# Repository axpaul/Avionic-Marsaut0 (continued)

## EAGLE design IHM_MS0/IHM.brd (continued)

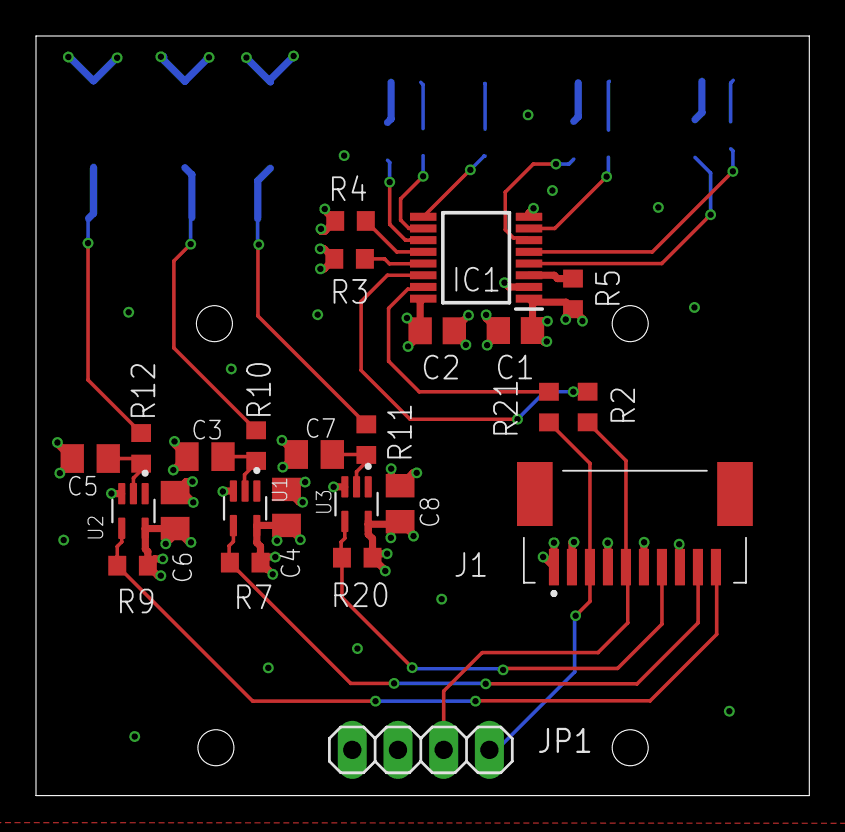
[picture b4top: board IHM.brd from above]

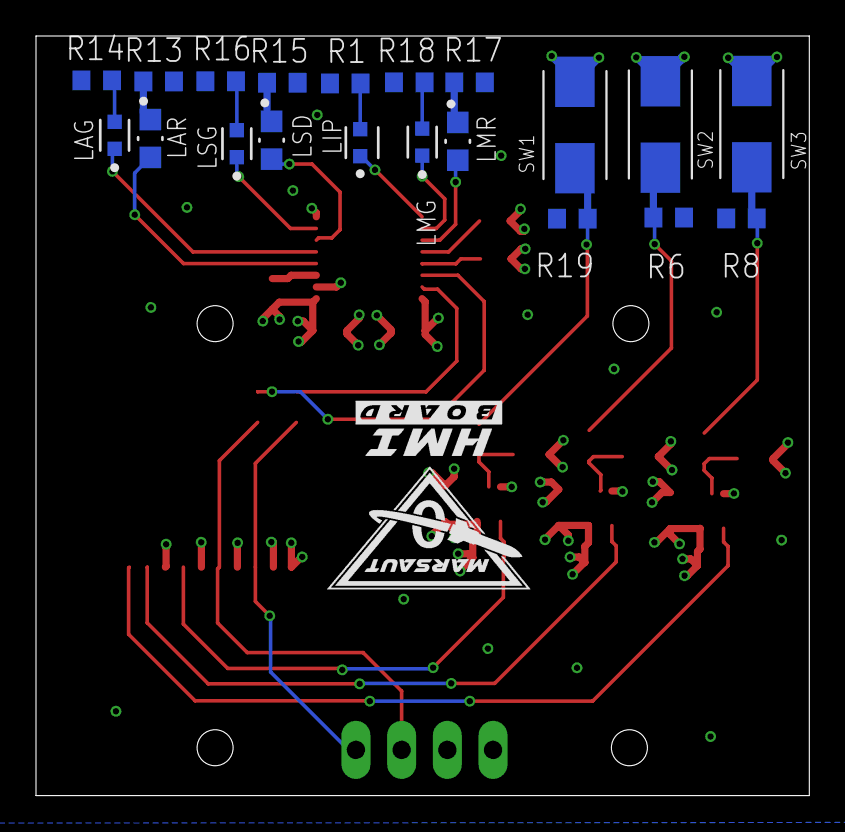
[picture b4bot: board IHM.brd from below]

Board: 4 copper layers, 43.0 x 42.2 mm, 45 parts (20 on the bottom side), 32 nets.

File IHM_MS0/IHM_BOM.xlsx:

Qty | Value | MPN | Package | Parts | Description | LCSC Part
1 |  | NON-CONNECTED | 1X04 | JP1 | PIN HEADER
3 | 0R | 0603WAF0000T5E | R0603 | R2, R4, R21 | RESISTOR, European symbol | C21189
5 | 100nF | CC0805KRX7R9BB104 | C0805K | C1, C2, C4, C6, C8 | CAPACITOR, European symbol | C49678
4 | 10K | 0603WAF1002T5E | R0603 | R3, R6, R7, R20 | RESISTOR, European symbol | C25804
7 | 110R | NON-CONNECTED | R0603 | R1, R13, R14, R15, R16, R17, R18 | RESISTOR, European symbol
3 | 147873-1 | NON-CONNECTED | SW_147873-1 | SW1, SW2, SW3 | Switch Tactile OFF (ON) SPST Rectangular Button J-Bend 0.05A 24VDC 1.77N SMD T/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
3 | 1K | 0603WAF1001T5E | R0603 | R10, R11, R12 | RESISTOR, European symbol | C21190
3 | 2u2F | 0805F225M500NT | C0805K | C3, C5, C7 | CAPACITOR, European symbol | C49217
1 | 4K7 | 0603WAF4701T5E | R0603 | R5 | RESISTOR, European symbol | C23162
3 | BROADCOM_ASMT-RF45-AN002BROADCOM_ASMT-RF45-AN002_0_0 | NON-CONNECTED | BROADCOM_ASMT-RF45-AN002_0 | LAG, LMG, LSG | LED YLW/GREEN DIFFUSED 0603 SMD
1 | BROADCOM_HSMA-C190BROADCOM_HSMA-C190_0_0 | NON-CONNECTED | BROADCOM_HSMA-C190_0 | LIP | Amber 592nm LED Indication - Discrete 1.9V 0603 (1608 Metric)
3 | BROADCOM_HSMH-C170BROADCOM_HSMH-C170_0_0 | NON-CONNECTED | BROADCOM_HSMH-C170_0 | LAR, LMR, LSD | LED RED DIFFUSED 0805 SMD
1 | FC1-10-02-T-WT-TR | NON-CONNECTED | FC11002TWTTR | J1 | FFC & FPC Connectors 1.00 mm Flat Flexible Cable (FFC) Socket Strip
3 | SN74LVC1G17DCKR | NON-CONNECTED | SOT65P210X110-5N | U1, U2, U3 | Check prices
1 | TCA6408AQPWRQ1 | NON-CONNECTED | SOP65P640X120-16N | IC1 | Automotive Low-Voltage 8-Bit I2C and SMBus I/O Expander With Interrupt Output

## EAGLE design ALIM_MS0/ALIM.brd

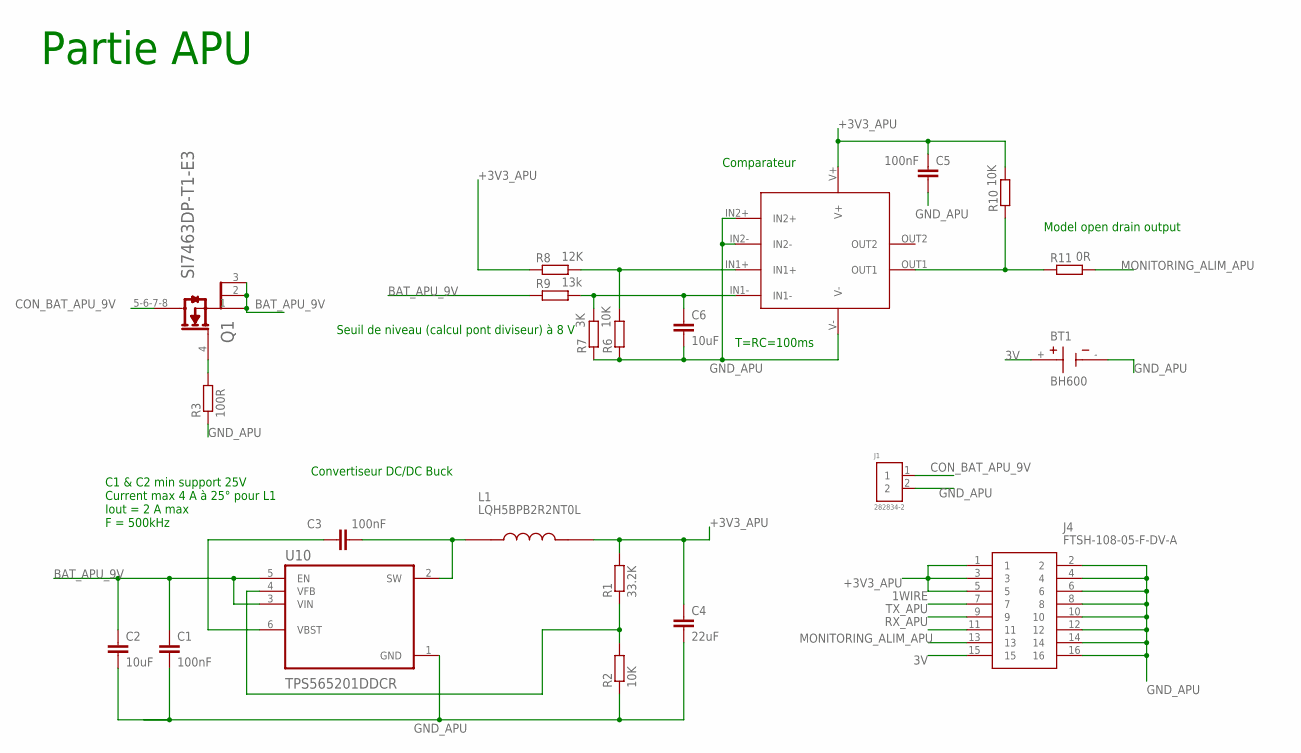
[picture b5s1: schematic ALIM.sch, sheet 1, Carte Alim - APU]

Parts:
BT1: BH600; BAT_BH600
C1, C3, C5: 100nF; C0805
C2, C6: 10uF; C0805
C4: 22uF; C0805
J1: 282834-2; CONN_282834-2
J4: FTSH-108-05-F-DV-A; FTSH-108-XX-YYY-DV-A
L1: LQH5BPB2R2NT0L; IND_LQH5BPB2R2NT0L
Q1: VISHAY_SI7463DP-T1-E3VISHAY_SI7463DP-T1-E3_0_0; VISHAY_SI7463DP-T1-E3_0
R1: 33.2K; R0603
R2, R6, R10: 10K; R0603
R3: 100R; R0603
R7: 3K; R0603
R8: 12K; R0603
R9: 13k; R0603
R11: 0R; R0603
TLV1: TLV9022
U10: TPS565201DDCR; SOT95P280X110-6N

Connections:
1WIRE: J4.7
3V: BT1.+, J4.15
+3V3_APU: C4.1, C5.1, J4.1, J4.3, J4.5, L1.2, R1.2, R8.1, R10.2, TLV1.V+
BAT_APU_9V: C1.1, C2.1, Q1.1 (1_S), Q1.2 (2_S), Q1.3 (3_S), R9.1, U10.3 (VIN), U10.5 (EN)
CON_BAT_APU_9V: J1.1, Q1.5-6-7-8 (D)
GND_APU: BT1.-, C1.2, C2.2, C4.2, C5.2, C6.2, J1.2, J4.2, J4.4, J4.6, J4.8, J4.10, J4.12, J4.14, J4.16, R2.1, R3.1, R6.1, R7.1, TLV1.IN2+, TLV1.IN2-, TLV1.V-, U10.1 (GND)
MONITORING_ALIM_APU: J4.13, R11.2
unnamed: Q1.4 (G), R3.2
unnamed: C3.1, U10.6 (VBST)
unnamed: C3.2, L1.1, U10.2 (SW)
unnamed: R1.1, R2.2, U10.4 (VFB)
unnamed: R6.2, R8.2, TLV1.IN1+
unnamed: C6.1, R7.2, R9.2, TLV1.IN1-
unnamed: R10.1, R11.1, TLV1.OUT1
RX_APU: J4.11
TX_APU: J4.9

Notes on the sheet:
C1 & C2 min support 25V Current max 4 A à 25° pour L1 Iout = 2 A max F = 500kHz
Model open drain output
T=RC=100ms
Comparateur
Convertiseur DC/DC Buck
Seuil de niveau (calcul pont diviseur) à 8 V
Partie APU

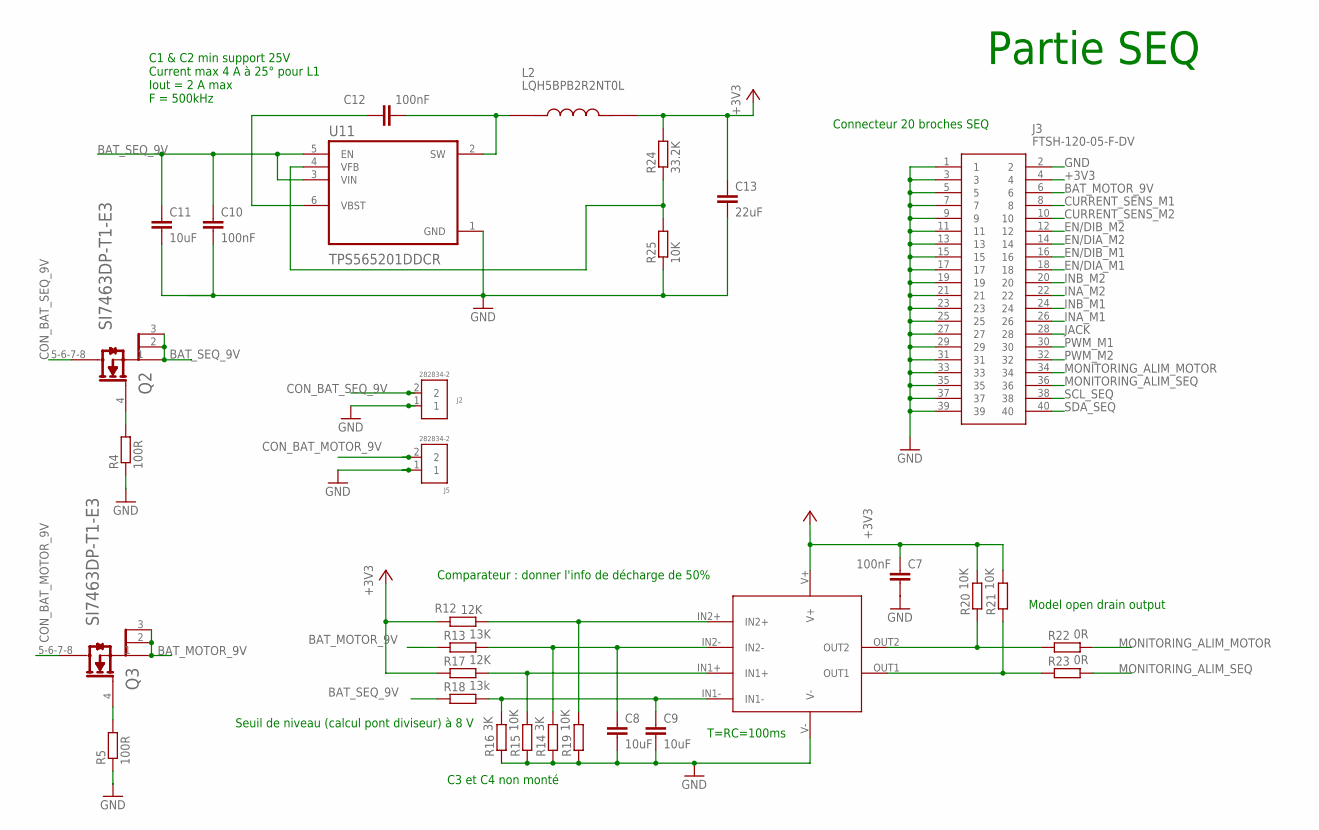
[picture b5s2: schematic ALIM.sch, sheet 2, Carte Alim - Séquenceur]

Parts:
C7, C10, C12: 100nF; C0805
C8, C9, C11: 10uF; C0805
C13: 22uF; C0805
J2, J5: 282834-2; CONN_282834-2
J3: FTSH-120-05-F-DV; FTSH-120-XX-YYY-DV
L2: LQH5BPB2R2NT0L; IND_LQH5BPB2R2NT0L
Q2, Q3: VISHAY_SI7463DP-T1-E3VISHAY_SI7463DP-T1-E3_0_0; VISHAY_SI7463DP-T1-E3_0
R4, R5: 100R; R0603
R12, R17: 12K; R0603
R13: 13K; R0603
R14, R16: 3K; R0603
R15, R19, R20, R21, R25: 10K; R0603
R18: 13k; R0603
R22, R23: 0R; R0603
R24: 33.2K; R0603
TLV2: TLV9022
U11: TPS565201DDCR; SOT95P280X110-6N

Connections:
+3V3: C7.1, C13.1, J3.4, L2.2, R12.2, R17.1, R20.2, R21.2, R24.2, TLV2.V+
BAT_MOTOR_9V: J3.6, Q3.1 (1_S), Q3.2 (2_S), Q3.3 (3_S), R13.1
BAT_SEQ_9V: C10.1, C11.1, Q2.1 (1_S), Q2.2 (2_S), Q2.3 (3_S), R18.1, U11.3 (VIN), U11.5 (EN)
CON_BAT_MOTOR_9V: J5.2, Q3.5-6-7-8 (D)
CON_BAT_SEQ_9V: J2.2, Q2.5-6-7-8 (D)
CURRENT_SENS_M1: J3.8
CURRENT_SENS_M2: J3.10
EN/DIA_M1: J3.18
EN/DIA_M2: J3.14
EN/DIB_M1: J3.16
EN/DIB_M2: J3.12
GND: C7.2, C8.2, C9.2, C10.2, C11.2, C13.2, J2.1, J3.1, J3.2, J3.3, J3.5, J3.7, J3.9, J3.11, J3.13, J3.15, J3.17, J3.19, J3.21, J3.23, J3.25, J3.27, J3.29, J3.31, J3.33, J3.35, J3.37, J3.39, J5.1, R4.1, R5.1, R14.1, R15.1, R16.1, R19.1, R25.1, TLV2.V-, U11.1 (GND)
INA_M1: J3.26
INA_M2: J3.22
INB_M1: J3.24
INB_M2: J3.20
JACK: J3.28
MONITORING_ALIM_MOTOR: J3.34, R22.2
MONITORING_ALIM_SEQ: J3.36, R23.2
unnamed: Q2.4 (G), R4.2
unnamed: Q3.4 (G), R5.2
unnamed: R12.1, R19.2, TLV2.IN2+
unnamed: C8.1, R13.2, R14.2, TLV2.IN2-
unnamed: R15.2, R17.2, TLV2.IN1+
unnamed: C9.1, R16.2, R18.2, TLV2.IN1-
unnamed: R20.1, R22.1, TLV2.OUT2
unnamed: R21.1, R23.1, TLV2.OUT1
unnamed: C12.1, U11.6 (VBST)
unnamed: C12.2, L2.1, U11.2 (SW)
unnamed: R24.1, R25.2, U11.4 (VFB)
PWM_M1: J3.30
PWM_M2: J3.32
SCL_SEQ: J3.38
SDA_SEQ: J3.40

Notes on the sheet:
C3 et C4 non monté
C1 & C2 min support 25V Current max 4 A à 25° pour L1 Iout = 2 A max F = 500kHz
Model open drain output
T=RC=100ms
Connecteur 20 broches SEQ
Comparateur : donner l'info de décharge de 50%
Seuil de niveau (calcul pont diviseur) à 8 V
Partie SEQ

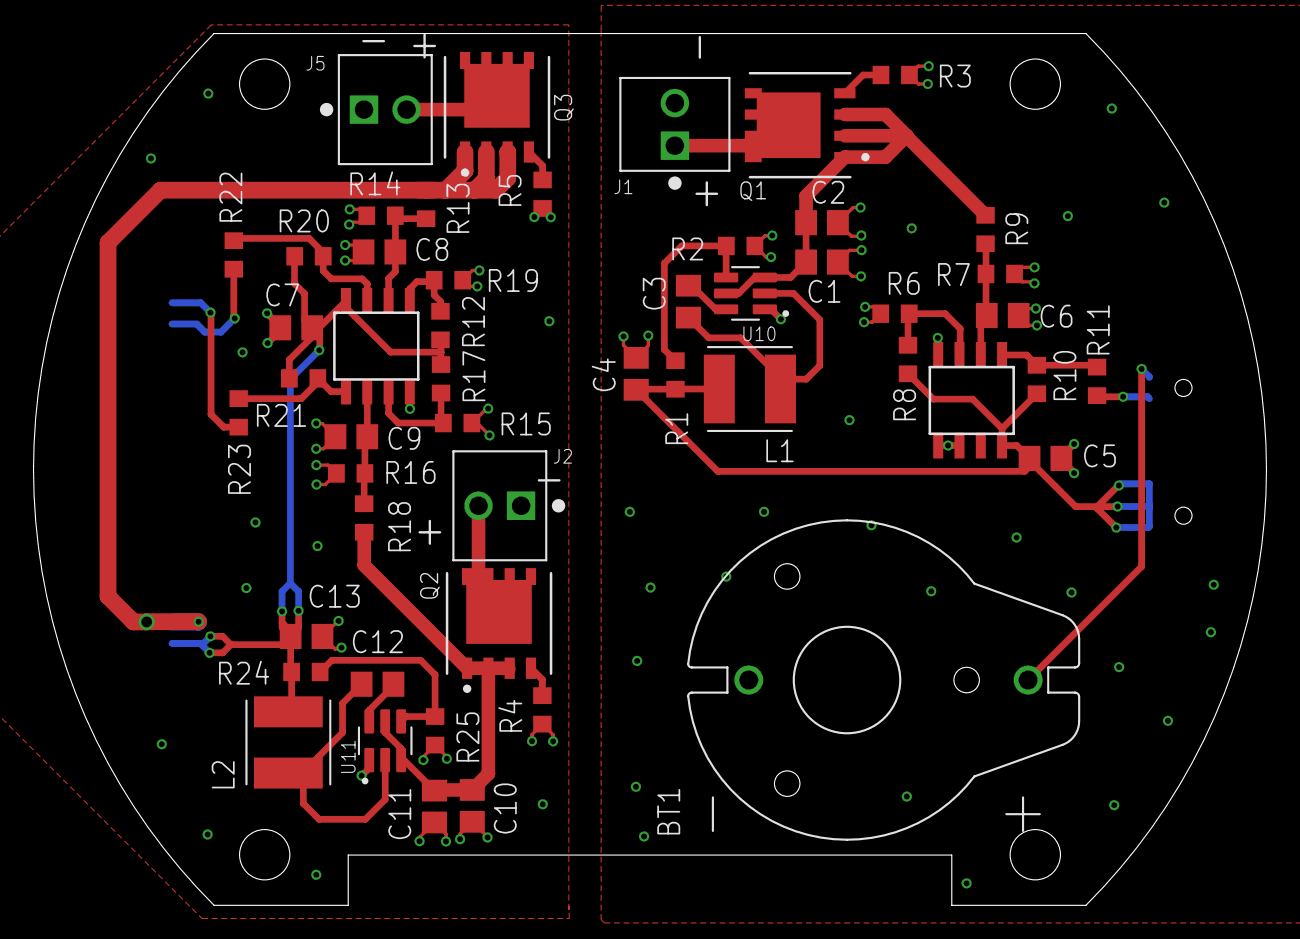
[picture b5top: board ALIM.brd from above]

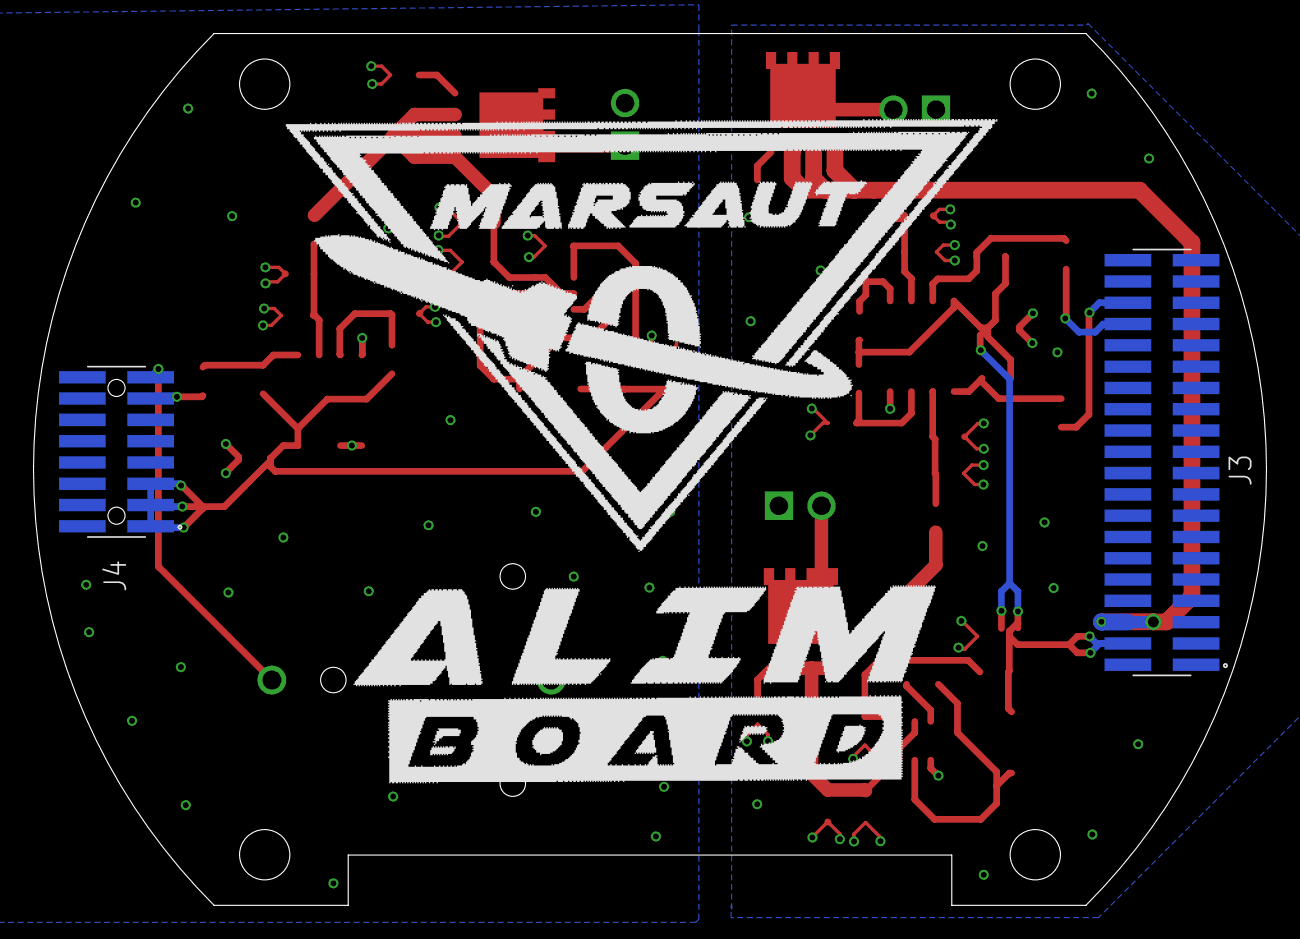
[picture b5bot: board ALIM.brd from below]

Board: 4 copper layers, 73.5 x 52.0 mm, 53 parts (2 on the bottom side), 32 nets.

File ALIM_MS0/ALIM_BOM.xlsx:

Qty | Value | MPN | Package | Parts | Description | LCSC Part Number(optional)
3 | 0R | 0603WAF0000T5E | R0603 | R11, R22, R23 | RESISTOR, European symbol | C21189
3 | 100R | NON-CONNECTED | R0603 | R3, R4, R5 | RESISTOR, European symbol
6 | 100nF | CC0805KRX7R9BB104 | C0805 | C1, C3, C5, C7, C10, C12 | CAPACITOR, European symbol | C49678
8 | 10K | 0603WAF1002T5E | R0603 | R2, R6, R10, R15, R19, R20, R21, R25 | RESISTOR, European symbol | C25804
5 | 10uF | CL21A106KAYNNNE | C0805 | C2, C6, C8, C9, C11 | CAPACITOR, European symbol | C15850
3 | 12K | 0603WAF1202T5E | R0603 | R8, R12, R17 | RESISTOR, European symbol | C22790
3 | 13K | 0603WAF1302T5E | R0603 | R9, R13, R18 | RESISTOR, European symbol | C22797
2 | 22uF | CL21A226MAQNNNE | C0805 | C4, C13 | CAPACITOR, European symbol | C45783
3 | 282834-2 | NON-CONNECTED | TROUGH HOLE | J1, J2, J5 | Terminal block; 2.54mm; angled 90Â°; 0.03Ã·1mm2; ways: 2; 10A; H: 10mm Check pr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
2 | 33K | 0603WAF3302T5E | R0603 | R1, R24 | RESISTOR, European symbol | C4216
3 | 3K | 0603WAF3001T5E | R0603 | R7, R14, R16 | RESISTOR, European symbol | C4211
1 | BH600 | NON-CONNECTED | BAT_BH600 | BT1 | BATTERY HOLDER COIN 16MM PC PIN Check prices
1 | FTSH-108-05-F-DV-A | NON-CONNECTED | CONNECTOR_SMT | J4 | 16 Position, High Reliability Header Strips, 0.050 pitch"
1 | FTSH-120-05-F-DV | NON-CONNECTED | CONNECTOR_SMT | J3 | 40 Position, High Reliability Header Strips, 0.050 pitch"
2 | LQH5BPB2R2NT0L | NON-CONNECTED | SMT | L1, L2 | Inductor Power Chip Shielded Wirewound 1.2uH 30% 100KHz Ferrite 3.1A 0.0228Ohm 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
2 | TLV9022DR | NON-CONNECTED | SOIC-8 | TLV1, TLV2
2 | TPS565201DDCR | NON-CONNECTED | SOT95P280X110-6N | U10, U11 | Check prices
3 | SI7463DP-T1-E3 | NON-CONNECTED | VISHAY_SI7463DP-T1-E3_0 | Q1, Q2, Q3 | MOSFET 40V 18.6A 5.4W 9.2mohm @ 10V

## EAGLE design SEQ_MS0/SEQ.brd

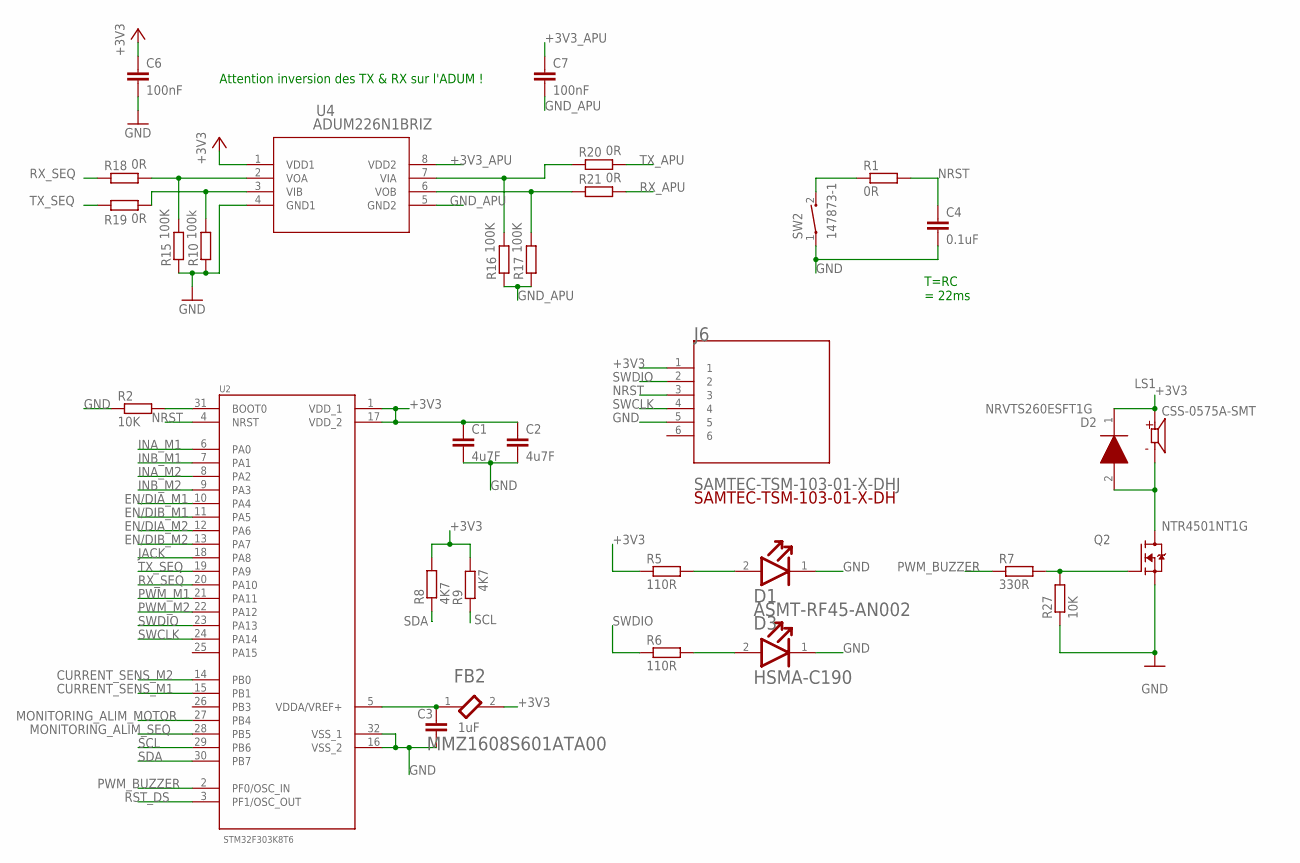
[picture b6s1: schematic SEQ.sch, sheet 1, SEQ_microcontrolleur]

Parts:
C1, C2: 4u7F; C0805K
C3: 1uF; C0805K
C4: 0.1uF; C0805K
C6, C7: 100nF; C0805
D1: BROADCOM_ASMT-RF45-AN002BROADCOM_ASMT-RF45-AN002_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; BROADCOM_ASMT-RF45-AN002_0
D2: NRVTS260ESFT1G; SODFL3616X98N
D3: BROADCOM_HSMA-C190BROADCOM_HSMA-C190_0_0; BROADCOM_HSMA-C190_0
FB2: TDK_MMZ1608S601ATA00TDK_MMZ1608S601ATA00_0_0; TDK_MMZ1608S601ATA00_0
J6: SAMTEC-TSM-103-01-X-DHJ; SAMTEC-TSM-103-01-X-DH
LS1: CSS-0575A-SMT; CUI_CSS-0575A-SMT
Q2: NTR4501NT1G; SOT95P237X111-3N
R1, R18, R19, R20, R21: 0R; R0603
R2, R27: 10K; R0603
R5, R6: 110R; R0603
R7: 330R; R0603
R8, R9: 4K7; R0603
R10: 100k; R0603
R15, R16, R17: 100K; R0603
SW2: 147873-1; SW_147873-1
U2: STM32F303K8T6; QFP80P900X900X160-32N
U4: ADUM226N1BRIZ; RI_8_1_ADI

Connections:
+3V3: C1.1, C2.1, C6.1, D2.1 (K), FB2.2, J6.1, LS1.1, R5.1, R8.2, R9.2, U2.1 (VDD_1), U2.17 (VDD_2), U4.1 (VDD1); also elsewhere on the board
+3V3_APU: C7.1, U4.8 (VDD2); also elsewhere on the board
CURRENT_SENS_M1: U2.15 (PB1); also elsewhere on the board
CURRENT_SENS_M2: U2.14 (PB0); also elsewhere on the board
EN/DIA_M1: U2.10 (PA4); also elsewhere on the board
EN/DIA_M2: U2.12 (PA6); also elsewhere on the board
EN/DIB_M1: U2.11 (PA5); also elsewhere on the board
EN/DIB_M2: U2.13 (PA7); also elsewhere on the board
GATE: Q2.1 (G), R7.2, R27.2
GND: C1.2, C2.2, C3.2, C4.2, C6.2, D1.1 (CATHODE), D3.1 (CATHODE), J6.5, Q2.2 (S), R2.1, R10.1, R15.1, R27.1, SW2.1, U2.16 (VSS_2), U2.32 (VSS_1), U4.4 (GND1); also elsewhere on the board
GND_APU: C7.2, R16.1, R17.1, U4.5 (GND2); also elsewhere on the board
INA_M1: U2.6 (PA0); also elsewhere on the board
INA_M2: U2.8 (PA2); also elsewhere on the board
INB_M1: U2.7 (PA1); also elsewhere on the board
INB_M2: U2.9 (PA3); also elsewhere on the board
JACK: U2.18 (PA8); also elsewhere on the board
MONITORING_ALIM_MOTOR: U2.27 (PB4); also elsewhere on the board
MONITORING_ALIM_SEQ: U2.28 (PB5); also elsewhere on the board
unnamed: C3.1, FB2.1, U2.5 (VDDA/VREF+)
unnamed: R2.2, U2.31 (BOOT0)
unnamed: R1.1, SW2.2
unnamed: D1.2 (ANODE), R5.2
unnamed: D3.2 (ANODE), R6.2
unnamed: R10.2, R19.2, U4.3 (VIB)
unnamed: R15.2, R18.2, U4.2 (VOA)
unnamed: R16.2, R20.1, U4.7 (VIA)
unnamed: R17.2, R21.1, U4.6 (VOB)
unnamed: D2.2 (A), LS1.2 (N), Q2.3 (D)
NRST: C4.1, J6.3, R1.2, U2.4 (NRST)
PWM_BUZZER: R7.1, U2.2 (PF0/OSC_IN)
PWM_M1: U2.21 (PA11); also elsewhere on the board
PWM_M2: U2.22 (PA12); also elsewhere on the board
RST_DS: U2.3 (PF1/OSC_OUT); also elsewhere on the board
RX_APU: R21.2; also elsewhere on the board
RX_SEQ: R18.1, U2.20 (PA10); also elsewhere on the board
SCL: R9.1, U2.29 (PB6); also elsewhere on the board
SDA: R8.1, U2.30 (PB7); also elsewhere on the board
SWCLK: J6.4, U2.24 (PA14)
SWDIO: J6.2, R6.1, U2.23 (PA13)
TX_APU: R20.2; also elsewhere on the board
TX_SEQ: R19.1, U2.19 (PA9); also elsewhere on the board

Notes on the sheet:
T=RC = 22ms
Attention inversion des TX & RX sur l'ADUM !

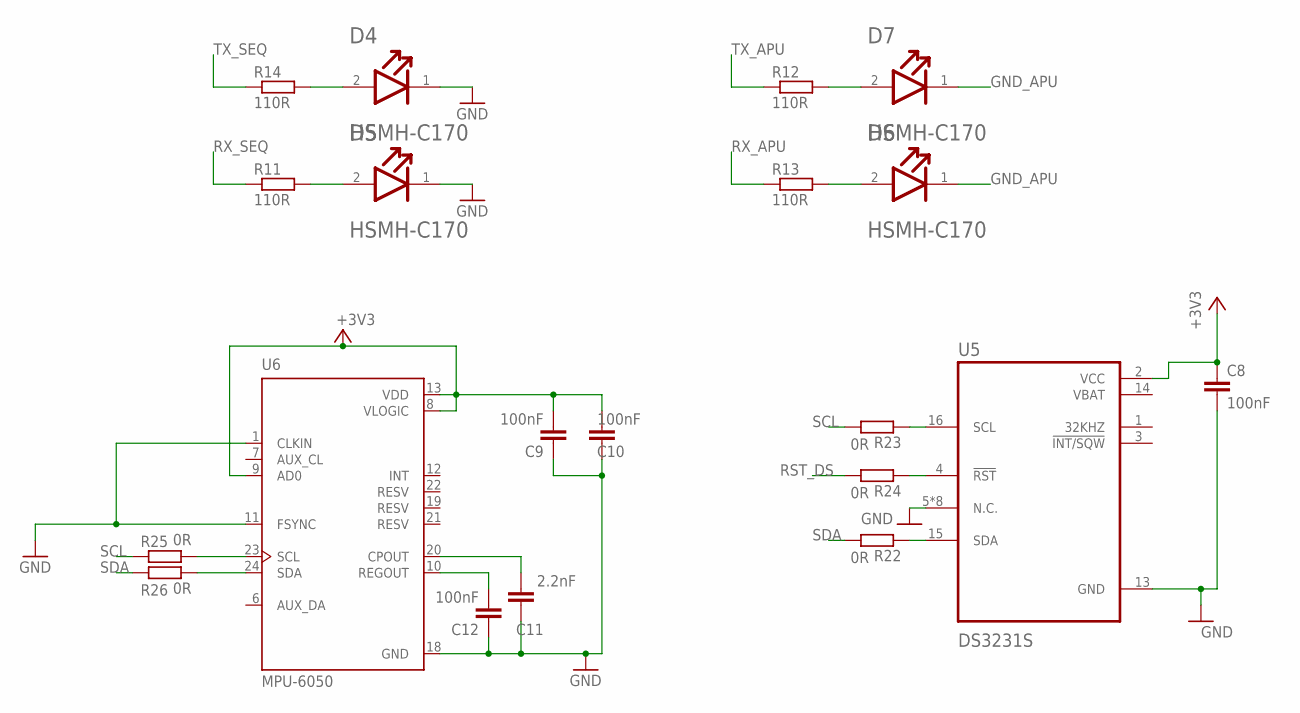
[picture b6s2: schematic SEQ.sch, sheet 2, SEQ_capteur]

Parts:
C8, C9, C10, C12: 100nF; C0805
C11: 2.2nF; C0805
D4, D5, D6, D7: BROADCOM_HSMH-C170BROADCOM_HSMH-C170_0_0; BROADCOM_HSMH-C170_0
R11, R12, R13, R14: 110R; R0603
R22, R23, R24, R25, R26: 0R; R0603
U5: DS3231S; SOIC127P1032X265-16N
U6: MPU-6050; QFN50P400X400X95-24N

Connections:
+3V3: C8.1, C9.2, C10.2, U5.2 (VCC), U6.8 (VLOGIC), U6.9 (AD0), U6.13 (VDD); also elsewhere on the board
GND: C8.2, C9.1, C10.1, C11.1, C12.1, D4.1 (CATHODE), D5.1 (CATHODE), U5.5 (N.C.), U5.6 (N.C.), U5.7 (N.C.), U5.8 (N.C.), U5.9 (N.C.), U5.10 (N.C.), U5.11 (N.C.), U5.12 (N.C.), U5.13 (GND), U6.1 (CLKIN), U6.11 (FSYNC), U6.18 (GND); also elsewhere on the board
GND_APU: D6.1 (CATHODE), D7.1 (CATHODE); also elsewhere on the board
unnamed: D4.2 (ANODE), R14.2
unnamed: D5.2 (ANODE), R11.2
unnamed: D7.2 (ANODE), R12.2
unnamed: D6.2 (ANODE), R13.2
unnamed: R22.1, U5.15 (SDA)
unnamed: R23.1, U5.16 (SCL)
unnamed: R24.1, U5.4 (!RST)
unnamed: R26.2, U6.24 (SDA)
unnamed: R25.2, U6.23 (SCL)
unnamed: C12.2, U6.10 (REGOUT)
unnamed: C11.2, U6.20 (CPOUT)
RST_DS: R24.2; also elsewhere on the board
RX_APU: R13.1; also elsewhere on the board
RX_SEQ: R11.1; also elsewhere on the board
SCL: R23.2, R25.1; also elsewhere on the board
SDA: R22.2, R26.1; also elsewhere on the board
TX_APU: R12.1; also elsewhere on the board
TX_SEQ: R14.1; also elsewhere on the board
VBAT: U5.14 (VBAT)

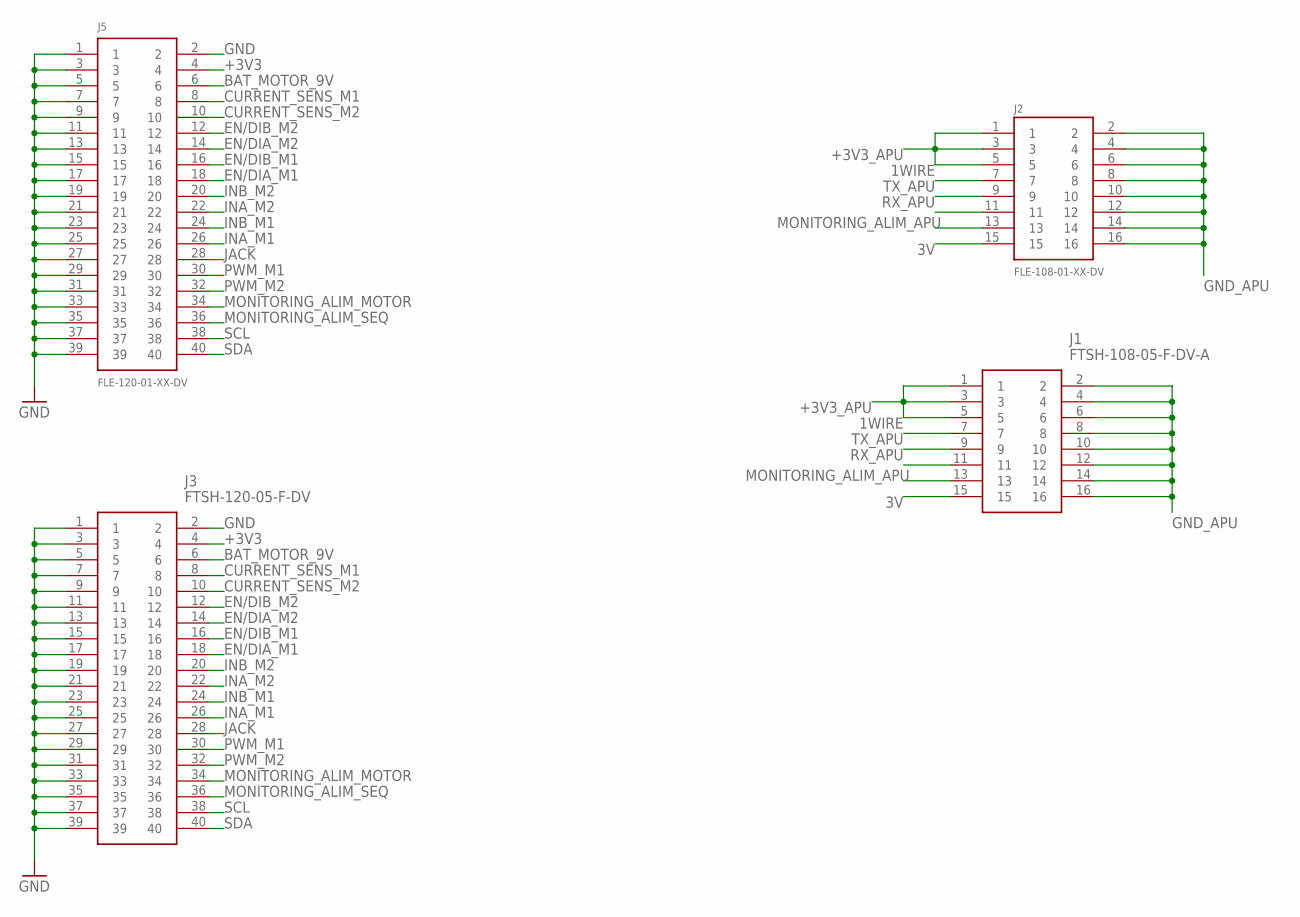
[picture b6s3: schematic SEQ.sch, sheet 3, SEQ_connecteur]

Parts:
J1: FTSH-108-05-F-DV-A; FTSH-108-XX-YYY-DV-A
J2: FLE-108-01-XX-DV
J3: FTSH-120-05-F-DV; FTSH-120-XX-YYY-DV
J5: FLE-120-01-XX-DV

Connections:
1WIRE: J1.7, J2.7
3V: J1.15, J2.15
+3V3: J3.4, J5.4; also elsewhere on the board
+3V3_APU: J1.1, J1.3, J1.5, J2.1, J2.3, J2.5; also elsewhere on the board
BAT_MOTOR_9V: J3.6, J5.6
CURRENT_SENS_M1: J3.8, J5.8; also elsewhere on the board
CURRENT_SENS_M2: J3.10, J5.10; also elsewhere on the board
EN/DIA_M1: J3.18, J5.18; also elsewhere on the board
EN/DIA_M2: J3.14, J5.14; also elsewhere on the board
EN/DIB_M1: J3.16, J5.16; also elsewhere on the board
EN/DIB_M2: J3.12, J5.12; also elsewhere on the board
GND: J3.1, J3.2, J3.3, J3.5, J3.7, J3.9, J3.11, J3.13, J3.15, J3.17, J3.19, J3.21, J3.23, J3.25, J3.27, J3.29, J3.31, J3.33, J3.35, J3.37, J3.39, J5.1, J5.2, J5.3, J5.5, J5.7, J5.9, J5.11, J5.13, J5.15, J5.17, J5.19, J5.21, J5.23, J5.25, J5.27, J5.29, J5.31, J5.33, J5.35, J5.37, J5.39; also elsewhere on the board
GND_APU: J1.2, J1.4, J1.6, J1.8, J1.10, J1.12, J1.14, J1.16, J2.2, J2.4, J2.6, J2.8, J2.10, J2.12, J2.14, J2.16; also elsewhere on the board
INA_M1: J3.26, J5.26; also elsewhere on the board
INA_M2: J3.22, J5.22; also elsewhere on the board
INB_M1: J3.24, J5.24; also elsewhere on the board
INB_M2: J3.20, J5.20; also elsewhere on the board
JACK: J3.28, J5.28; also elsewhere on the board
MONITORING_ALIM_APU: J1.13, J2.13
MONITORING_ALIM_MOTOR: J3.34, J5.34; also elsewhere on the board
MONITORING_ALIM_SEQ: J3.36, J5.36; also elsewhere on the board
PWM_M1: J3.30, J5.30; also elsewhere on the board
PWM_M2: J3.32, J5.32; also elsewhere on the board
RX_APU: J1.11, J2.11; also elsewhere on the board
SCL: J3.38, J5.38; also elsewhere on the board
SDA: J3.40, J5.40; also elsewhere on the board
TX_APU: J1.9, J2.9; also elsewhere on the board

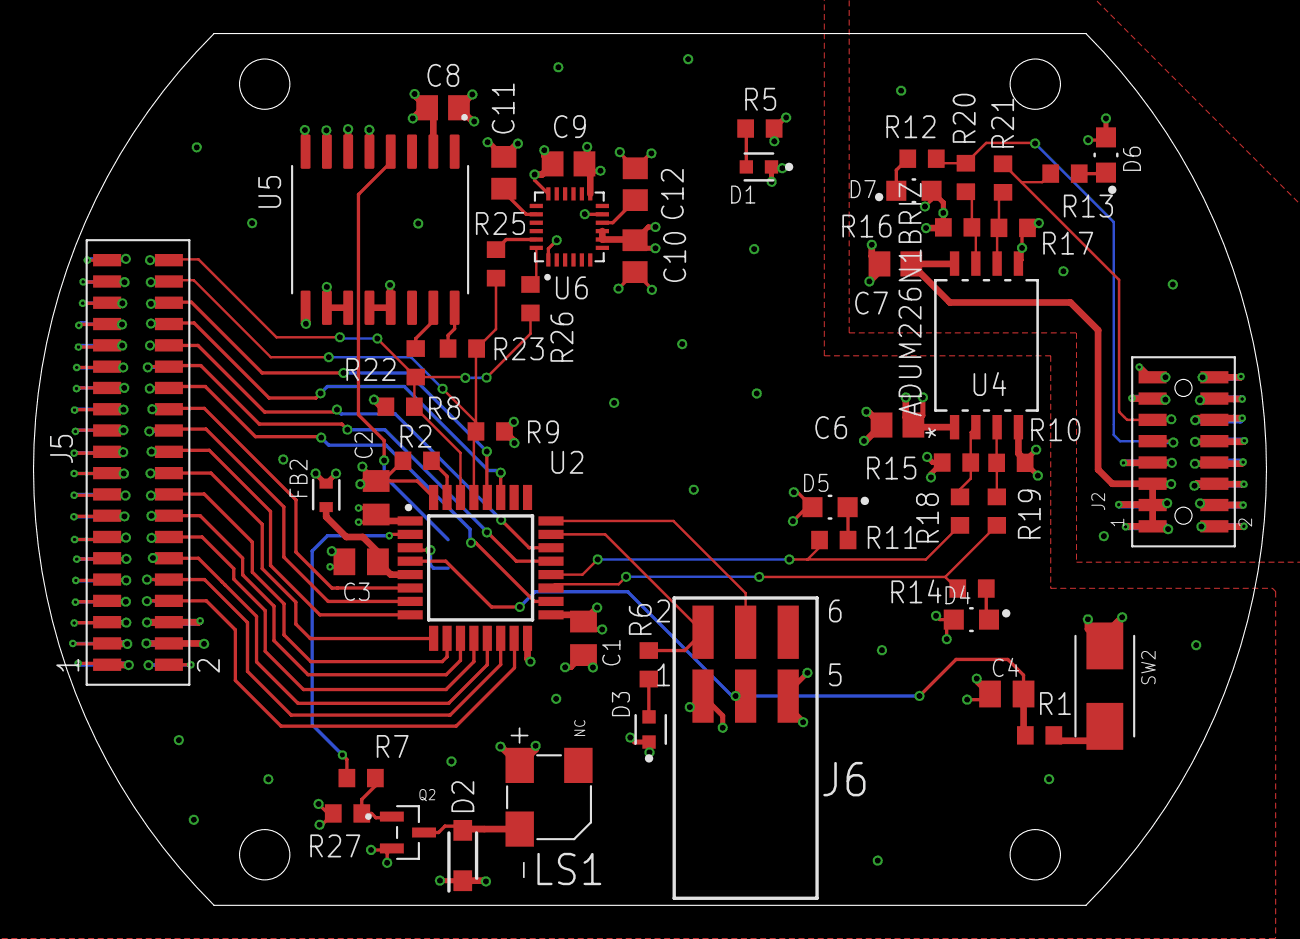
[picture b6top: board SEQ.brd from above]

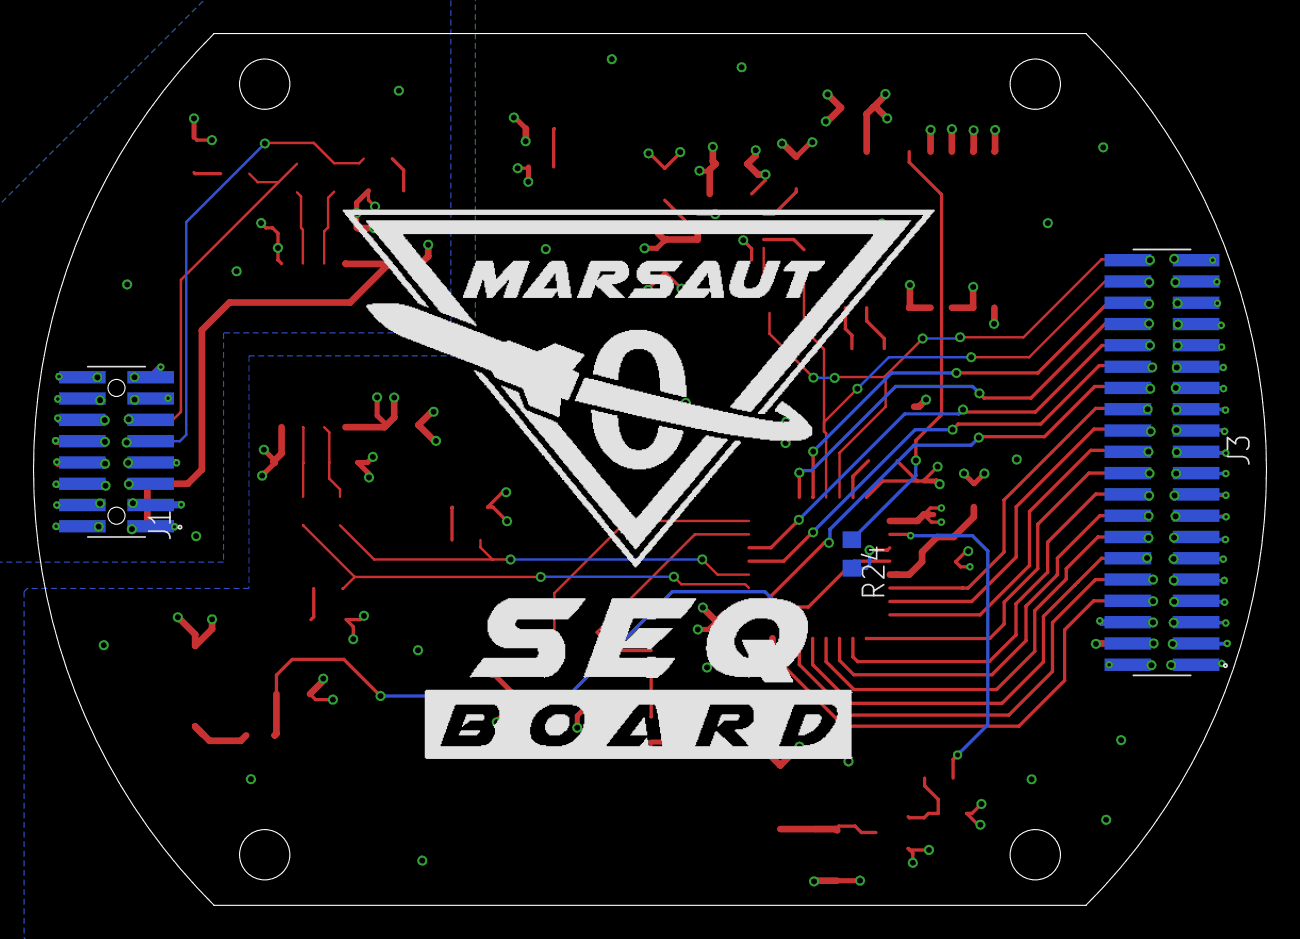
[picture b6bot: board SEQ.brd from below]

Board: 4 copper layers, 73.5 x 52.0 mm, 56 parts (3 on the bottom side), 56 nets.

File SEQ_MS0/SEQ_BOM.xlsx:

Qty | Value | MPN | Package | Parts
10 | 0R | CRCW06030000Z0EAC | R0603 | R1,R18, R19, R20, R21, R22, R23, R25, R26, R24
4 | 100K | ERJ-UP3D1003V | R0603 | R10, R15, R16, R17
6 | 100nF | C0805X104M5RACTU | C0805 | C6, C7, C8, C9, C10, C12
2 | 10K | ERJ-UP3F1002V | R0603 | R2, R27
6 | 110R | ERJ-UP3F1100V | R0603 | R5, R6, R11, R12, R13, R14
1 | 147873-1 |  | SW_147873-1 | SW2
1 | 330R | ERJ-UP3D1001V | R0603 | R7
1 | 1uF | C0805X105K3RAC3316 | C0805K | C3
1 | 2.2nF | C0805C222K3GECTU | C0805 | C11
1 | 2u2F | C0805C225K3RACTU | C0805K | C4
2 | 4K7 | ERJ-UP3D4701V | R0603 | R8, R9
2 | 4u7F | C0805C475K3RACTU | C0805K | C1, C2
1 | ADUM226N1BRIZ | ADUM226N1BRIZ | RI_8_1_ADI | U4
1 | BROADCOM_ASMT-RF45-AN002BROADCOM_ASMT-RF45-AN002_0_0 | ASMT-RF45-AN002 | BROADCOM_ASMT-RF45-AN002_0 | D1
1 | BROADCOM_HSMA-C190BROADCOM_HSMA-C190_0_0 | HSMA-C190 | BROADCOM_HSMA-C190_0 | D3
4 | BROADCOM_HSMH-C170BROADCOM_HSMH-C170_0_0 | HSMH-C170 | BROADCOM_HSMH-C170_0 | D4, D5, D6, D7
1 | CSS-0575A-SMT | CSS-0575A-SMT-TR | CUI_CSS-0575A-SMT | LS1
1 | DS3231S | DS3231S# | SOIC127P1032X265-16N | U5
1 | FLE-108-01-XX-DV | FLE-108-01-G-DV | FLE-108-01-XX-DV | J2
1 | FLE-120-01-XX-DV | FLE-120-01-G-DV | FLE-120-01-XX-DV | J5
1 | FTSH-108-05-F-DV-A | FTSH-108-05-F-DV-A | FTSH-108-XX-YYY-DV-A | J1
1 | FTSH-120-05-F-DV | FTSH-120-05-F-DV | FTSH-120-XX-YYY-DV | J3
1 | MPU-6050 | MPU-6050 | QFN50P400X400X95-24N | U6
1 | NRVTS260ESFT1G | RBR2MM40CTFTR | SODFL3616X98N | D2
1 | NTR4501NT1G | NTR4501NT1G | SOT95P237X111-3N | Q2
1 | SAMTEC-TSM-103-01-X-DHJ | TSM-103-01-F-DV-P-TR | SAMTEC-TSM-103-01-X-DH | J6
1 | SN74LVC1G17DCKR | SN74LVC1G17DCKR | SOT65P210X110-5N | U3
1 | STM32F303K8T6 | STM32F303K8T6 | QFP80P900X900X160-32N | U2
1 | TDK_MMZ1608S601ATA00TDK_MMZ1608S601ATA00_0_0 | MMZ1608S601ATA00 | TDK_MMZ1608S601ATA00_0 | FB2

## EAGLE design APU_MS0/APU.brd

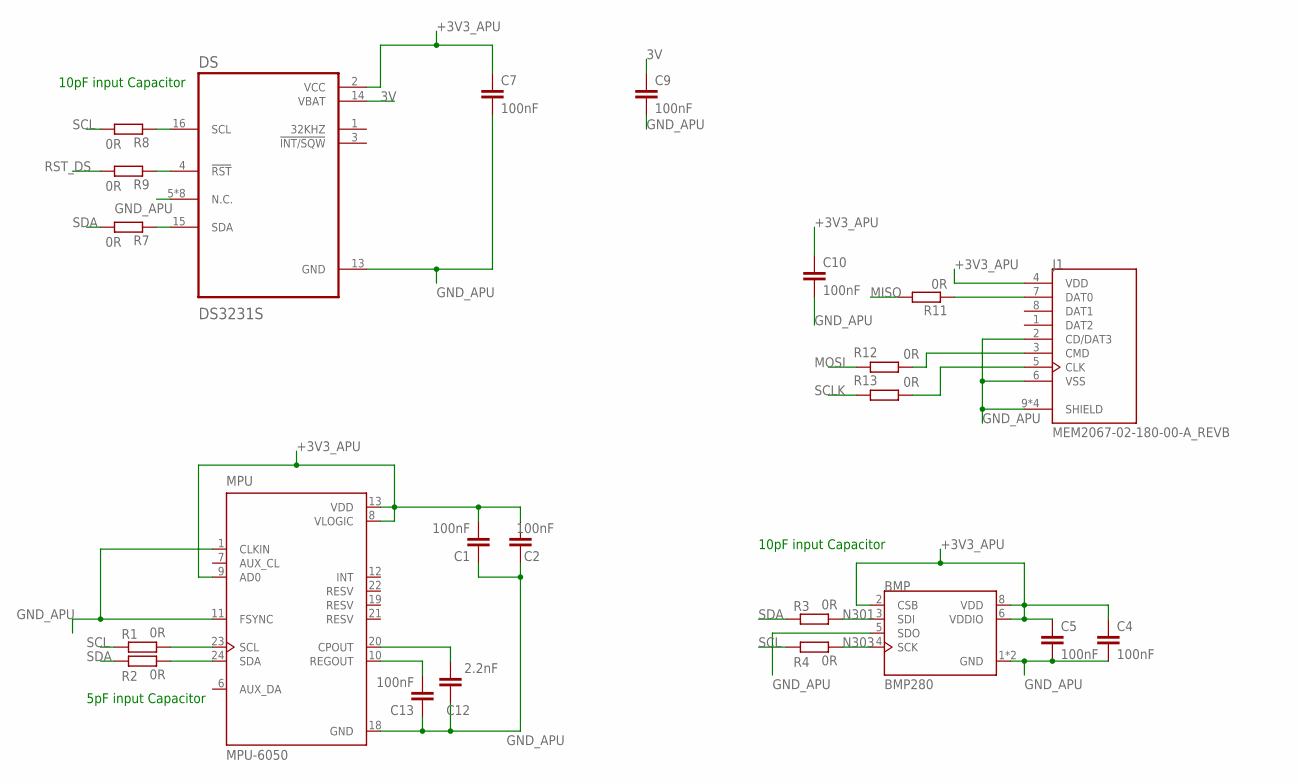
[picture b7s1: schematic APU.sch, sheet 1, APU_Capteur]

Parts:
BMP: BMP280; XDCR_BMP280
C1, C2, C4, C5, C7, C9, C10, C13: 100nF; C0805
C12: 2.2nF; C0805
DS: DS3231S; SOIC127P1032X265-16N
J1: MEM2067-02-180-00-A_REVB; GCT_MEM2067-02-180-00-A_REVB
MPU: MPU-6050; QFN50P400X400X95-24N
R1, R2, R3, R4, R7, R8, R9, R11, R12, R13: 0R; R0603

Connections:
3V: C9.1, DS.14 (VBAT); also elsewhere on the board
+3V3_APU: BMP.2 (CSB), BMP.6 (VDDIO), BMP.8 (VDD), C1.2, C2.2, C4.1, C5.1, C7.1, C10.1, DS.2 (VCC), J1.4 (VDD), MPU.8 (VLOGIC), MPU.9 (AD0), MPU.13 (VDD); also elsewhere on the board
GND_APU: BMP.1 (GND), BMP.5 (SDO), BMP.7 (GND), C1.1, C2.1, C4.2, C5.2, C7.2, C9.2, C10.2, C12.1, C13.1, DS.5 (N.C.), DS.6 (N.C.), DS.7 (N.C.), DS.8 (N.C.), DS.9 (N.C.), DS.10 (N.C.), DS.11 (N.C.), DS.12 (N.C.), DS.13 (GND), J1.2 (CD/DAT3), J1.6 (VSS), J1.9 (SHIELD), J1.10 (SHIELD), J1.11 (SHIELD), J1.12 (SHIELD), MPU.1 (CLKIN), MPU.11 (FSYNC), MPU.18 (GND); also elsewhere on the board
MISO: R11.2; also elsewhere on the board
MOSI: R12.2; also elsewhere on the board
N301: BMP.3 (SDI), R3.2
N303: BMP.4 (SCK), R4.2
unnamed: MPU.24 (SDA), R2.2
unnamed: MPU.23 (SCL), R1.2
unnamed: C13.2, MPU.10 (REGOUT)
unnamed: DS.15 (SDA), R7.1
unnamed: DS.16 (SCL), R8.1
unnamed: DS.4 (!RST), R9.1
unnamed: J1.7 (DAT0), R11.1
unnamed: J1.5 (CLK), R13.1
unnamed: J1.3 (CMD), R12.1
unnamed: C12.2, MPU.20 (CPOUT)
RST_DS: R9.2; also elsewhere on the board
SCL: R1.1, R4.1, R8.2; also elsewhere on the board
SCLK: R13.2; also elsewhere on the board
SDA: R2.1, R3.1, R7.2; also elsewhere on the board

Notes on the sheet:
5pF input Capacitor
10pF input Capacitor
